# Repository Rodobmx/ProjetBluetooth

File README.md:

ProjetBluetooth
===============

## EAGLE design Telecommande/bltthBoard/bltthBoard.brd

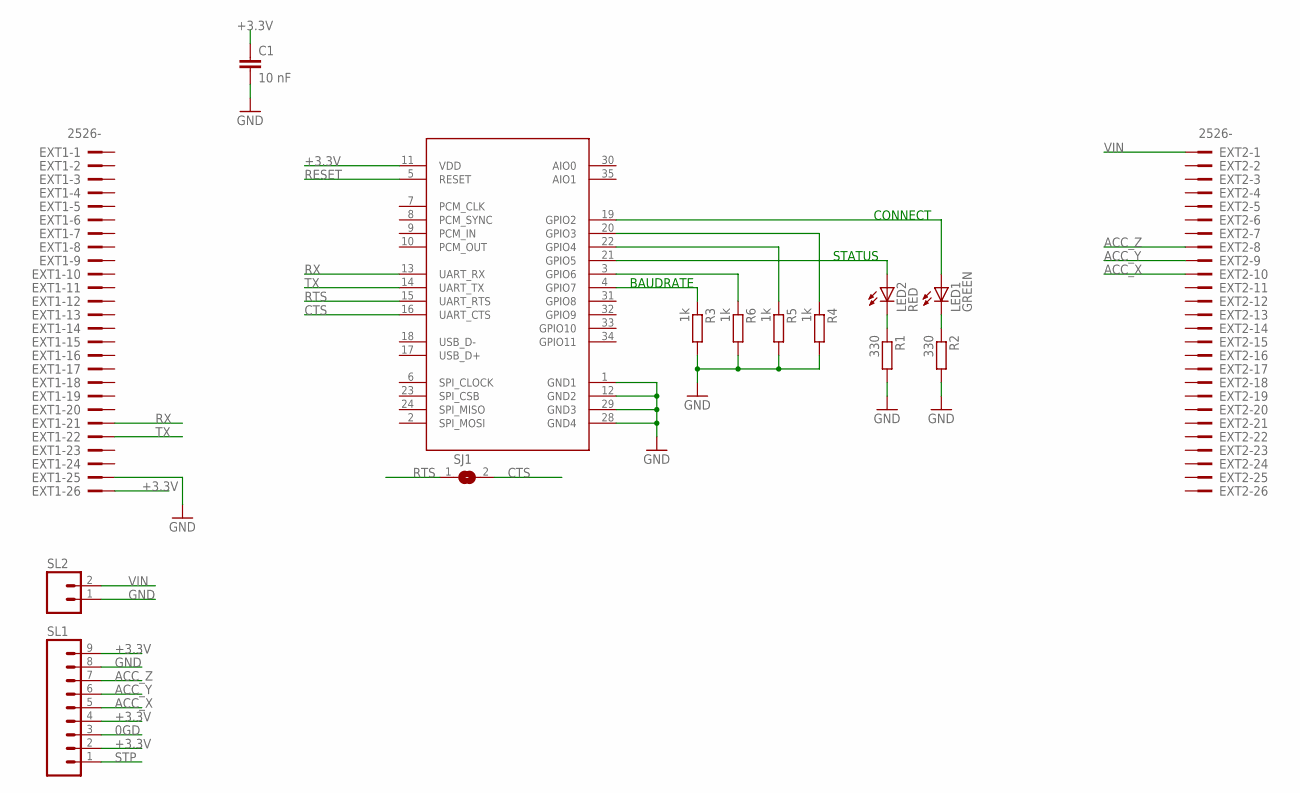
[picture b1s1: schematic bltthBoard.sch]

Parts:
C1: 10 nF; C0402
EXT1, EXT2: 2526-; PAK100/2500-26
LED1: GREEN; CHIP-LED0805
LED2: RED; CHIP-LED0805
R1, R2: 330; M0805
R3, R4, R5, R6: 1k; M0805
SJ1: SJ
SL1: M09; 09P
SL2: M02; 02P
U$1: U1; BLUETOOTH-RN42

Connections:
0GD: SL1.3
+3.3V: C1.1, EXT1.26, SL1.2, SL1.4, SL1.9, U$1.11 (VDD)
ACC_X: EXT2.10, SL1.5
ACC_Y: EXT2.9, SL1.6
ACC_Z: EXT2.8, SL1.7
CTS: SJ1.2, U$1.16 (UART_CTS)
GND: C1.2, EXT1.25, R1.2, R2.2, R3.2, R4.2, R5.2, R6.2, SL1.8, SL2.1, U$1.1 (GND1), U$1.12 (GND2), U$1.28 (GND4), U$1.29 (GND3)
unnamed: LED2.A, U$1.21 (GPIO5)
unnamed: LED1.C, R2.1
unnamed: LED2.C, R1.1
unnamed: R3.1, U$1.4 (GPIO7)
unnamed: R4.1, U$1.20 (GPIO3)
unnamed: R5.1, U$1.22 (GPIO4)
unnamed: R6.1, U$1.3 (GPIO6)
RESET: U$1.5 (RESET)
RTS: SJ1.1, U$1.15 (UART_RTS)
RX: EXT1.21, U$1.13 (UART_RX)
STATUS: LED1.A, U$1.19 (GPIO2)
STP: SL1.1
TX: EXT1.22, U$1.14 (UART_TX)
VIN: EXT2.1, SL2.2

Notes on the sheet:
CONNECT
STATUS
BAUDRATE

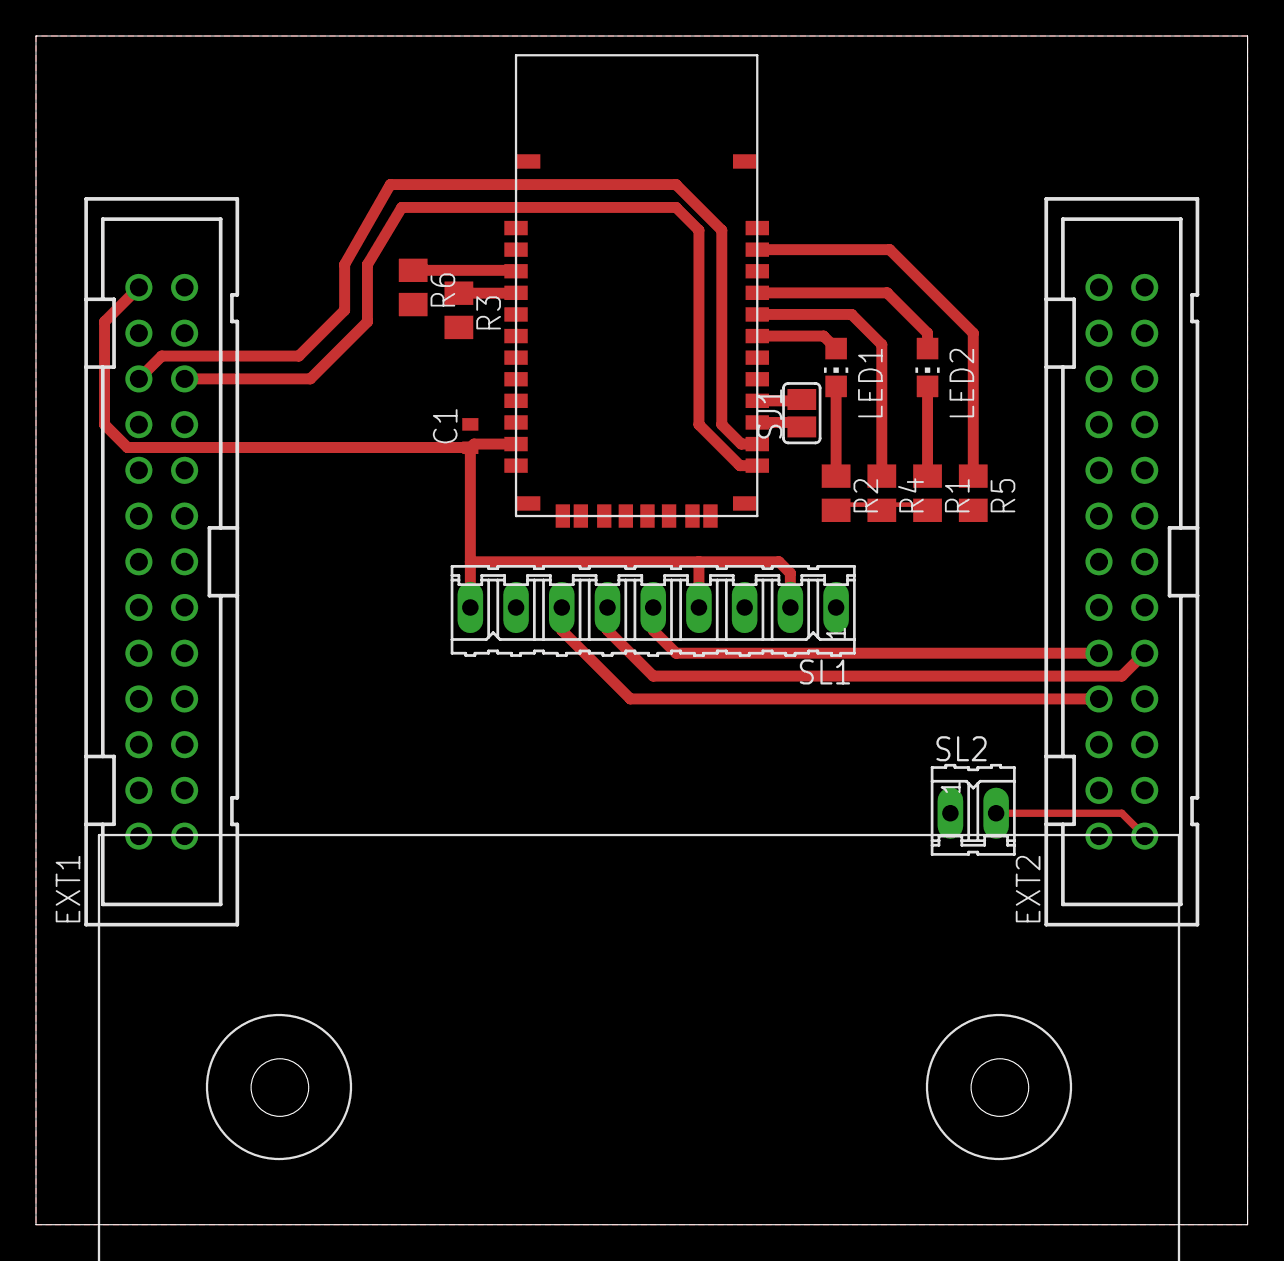
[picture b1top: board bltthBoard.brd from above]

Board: 2 copper layers, 67.3 x 66.0 mm, 16 parts (0 on the bottom side), 18 nets.

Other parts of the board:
U$3: SUPPORTDEPLIELR6

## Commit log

2013-03-31 Organisation des fichiers
    A verifier
2013-03-31 Réintégration fcts pilotage moteurs
2013-04-08 Correction des bugs concernant la réception des trames provenant de la manette (code en Python -> MSP430). Tests effectués la carte v1.5 -> OK
    A VERIFIER : la gestion des moteurs (PWM)
2013-04-09 Maj
    Ajout de la fonction de réception d'une trame sur le port série (attente
    du 1er caractère spécifique)
    TOCHK : Intégration des fonctions de pilotage des moteur (conflit)
2013-04-09 Code presque final. Moteur fonctionnel (P2.1 et P2.4), Uart en test.
2013-04-09 Légeres modifs. Coté UART toujours pas résolu
2013-05-09 Code manette
    Possibilité de changer le port com
2013-05-09 maj robot
2013-05-14 Maj code manette
    refonte du code principal + code spécifique pour les tests PWM du robot
2013-05-16 Reorganisation
2013-05-21 Ajout du code de la télécommande
2013-05-22 Maj de ce matin
